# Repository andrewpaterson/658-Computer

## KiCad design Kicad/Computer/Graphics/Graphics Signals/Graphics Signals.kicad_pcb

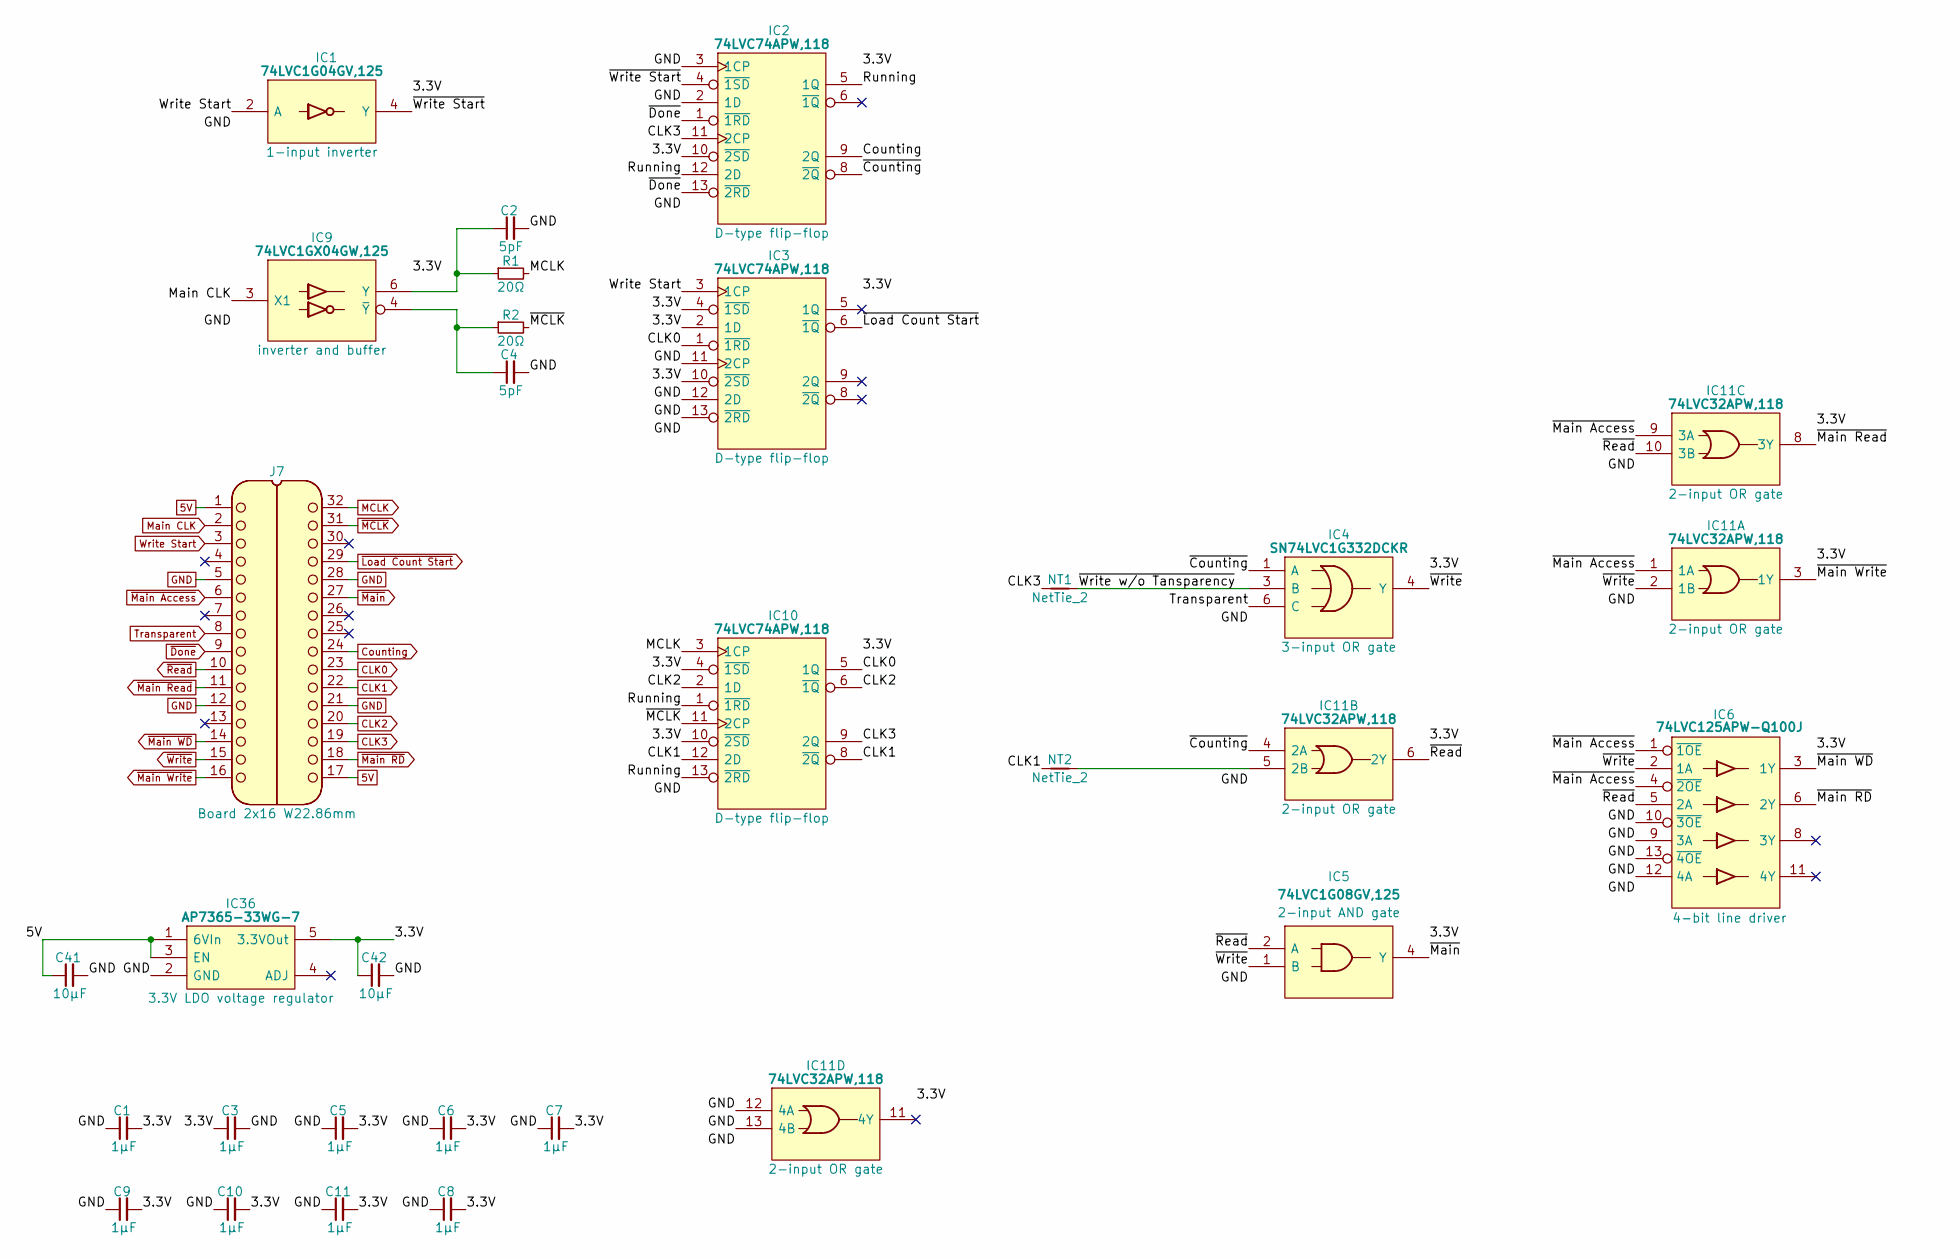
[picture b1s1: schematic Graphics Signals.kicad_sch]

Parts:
C1, C3, C5, C6, C7, C8, C9, C10, C11: 1μF; C_0805
C2, C4: 5pF; C_0805
C41, C42: 10μF; C_0805
IC1: 74LVC1G04GV,125; SOT95P275X110-5N; Manufacturer_Part_Number 74LVC1G04GV,125; Mouser Part Number 771-74LVC1G04GV
IC2, IC3, IC10: 74LVC74APW,118; SOP65P640X110-14N; Mouser Part Number 771-74LVC74APW-T
IC4: SN74LVC1G332DCKR; SOT65P210X110-6N; Mouser Part Number 595-SN74LVC1G332DCKR
IC5: 74LVC1G08GV,125; SOT95P275X110-5N; Manufacturer_Part_Number 74LVC1G08GV,125; Mouser Part Number 771-74LVC1G08GV
IC6: 74LVC125APW-Q100J; SOP65P640X110-14N; Manufacturer_Part_Number 74LVC125APW-Q100J; Mouser Part Number 771-74LVC125APWQ100J
IC9: 74LVC1GX04GW,125; SOP65P210X110-6N; Manufacturer_Part_Number 74LVC1GX04GW,125; Mouser Part Number 771-74LVC1GX04GW-G
IC11: 74LVC32APW,118; SOP65P640X110-14N; Manufacturer_Part_Number 74LVC32APW,118; Mouser Part Number 771-74LVC32APW-T
IC36: AP7365-33WG-7; SOT95P285X130-5N; Manufacturer_Part_Number AP7365-33WG-7; Mouser Part Number 621-AP7365-33WG-7
J7: Board 2x16 W22.86mm; DIP-32_Board_W22.86mm
NT1, NT2: NetTie_2; NetTie-2_SMD_Pad0.5mm
R1, R2: 20Ω; R_0805

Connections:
5V: C41.1, IC36.1 (6VIn), IC36.3 (EN), J7.1, J7.17
/3.3V: C1.2, C3.1, C5.2, C6.2, C7.2, C8.2, C9.2, C10.2, C11.2, C42.1, IC1.5 (3V), IC2.10 (~2SD), IC2.14 (3V), IC3.2 (1D), IC3.4 (~1SD), IC3.10 (~2SD), IC3.14 (3V), IC4.5 (3V), IC5.5 (3V), IC6.14 (3V), IC9.5 (3V), IC10.4 (~1SD), IC10.10 (~2SD), IC10.14 (3V), IC11.14 (3V), IC36.5 (3.3VOut)
/Running: IC2.5 (1Q), IC2.12 (2D), IC10.1 (~1RD), IC10.13 (~2RD)
/~Counting: IC2.8 (~2Q), IC4.1 (A), IC11.4 (2A)
/~Write Start: IC1.4 (Y), IC2.4 (~1SD)
/~Write w/o Tansparency: IC4.3 (B), NT1.2
CLK0: IC3.1 (~1RD), IC10.5 (1Q), J7.23
CLK1: IC10.8 (~2Q), IC10.12 (2D), J7.22, NT2.1
CLK2: IC10.2 (1D), IC10.6 (~1Q), J7.20
CLK3: IC2.11 (2CP), IC10.9 (2Q), J7.19, NT1.1
Counting: IC2.9 (2Q), J7.24
GND: C1.1, C2.2, C3.2, C4.2, C5.1, C6.1, C7.1, C8.1, C9.1, C10.1, C11.1, C41.2, C42.2, IC1.3 (GND), IC2.2 (1D), IC2.3 (1CP), IC2.7 (GND), IC3.7 (GND), IC3.11 (2CP), IC3.12 (2D), IC3.13 (~2RD), IC4.2 (GND), IC5.3 (GND), IC6.7 (GND), IC6.9 (3A), IC6.10 (~3OE), IC6.12 (4A), IC6.13 (~4OE), IC9.2 (GND), IC10.7 (GND), IC11.7 (GND), IC11.12 (4A), IC11.13 (4B), IC36.2 (GND), J7.5, J7.12, J7.21, J7.28
MCLK: IC10.3 (1CP), J7.32, R1.2
Main CLK: IC9.3 (X1), J7.2
unnamed: C2.1, IC9.6 (Y), R1.1
unnamed: C4.1, IC9.4 (~Y), R2.1
unnamed: IC11.5 (2B), NT2.2
Transparent: IC4.6 (C), J7.8
Write Start: IC1.2 (A), IC3.3 (1CP), J7.3
~Done: IC2.1 (~1RD), IC2.13 (~2RD), J7.9
~Load Count Start: IC3.6 (~1Q), J7.29
~MCLK: IC10.11 (2CP), J7.31, R2.2
~Main Access: IC6.1 (~1OE), IC6.4 (~2OE), IC11.1 (1A), IC11.9 (3A), J7.6
~Main RD: IC6.6 (2Y), J7.18
~Main Read: IC11.8 (3Y), J7.11
~Main WD: IC6.3 (1Y), J7.14
~Main Write: IC11.3 (1Y), J7.16
~Main: IC5.4 (Y), J7.27
~Read: IC5.2 (A), IC6.5 (2A), IC11.6 (2Y), IC11.10 (3B), J7.10
~Write: IC4.4 (Y), IC5.1 (B), IC6.2 (1A), IC11.2 (1B), J7.15

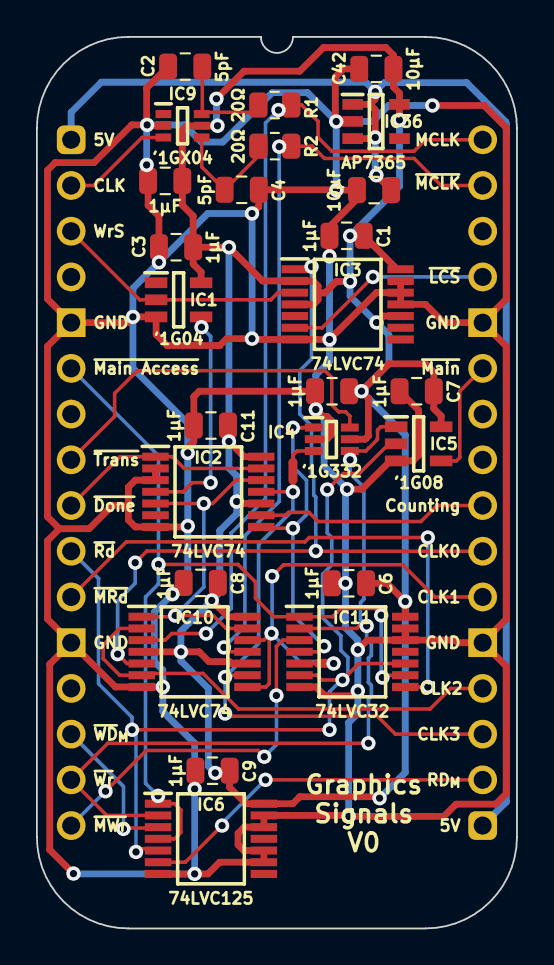
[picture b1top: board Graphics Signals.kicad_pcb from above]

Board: 2 copper layers, 26.7 x 49.5 mm, 28 parts (0 on the bottom side), 30 nets.

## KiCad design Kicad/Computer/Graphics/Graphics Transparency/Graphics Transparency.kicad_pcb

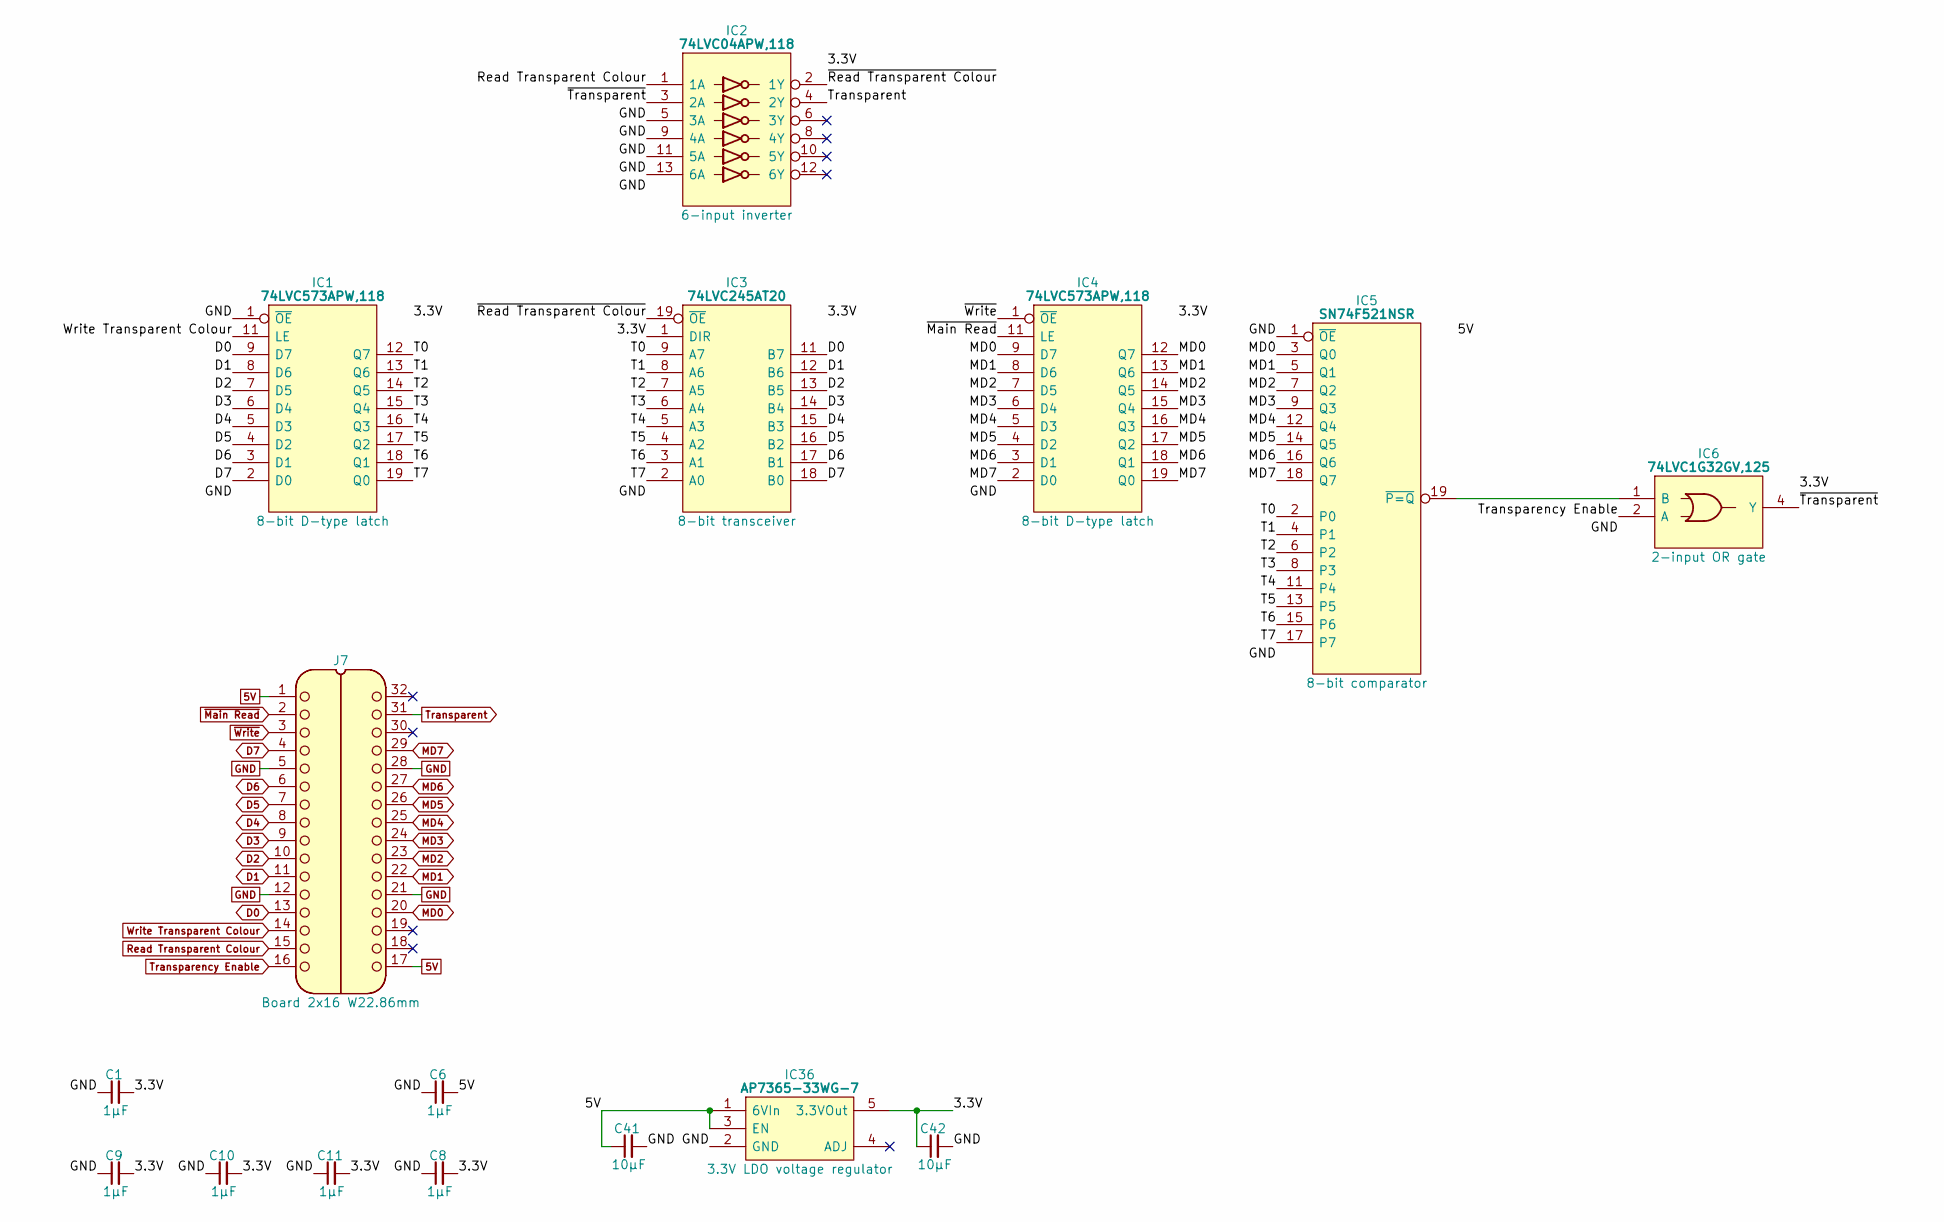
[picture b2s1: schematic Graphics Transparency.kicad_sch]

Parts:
C1, C6, C8, C9, C10, C11: 1μF; C_0805
C41, C42: 10μF; C_0805
IC1, IC4: 74LVC573APW,118; SOP65P640X110-20N; Mouser Part Number 771-74LVC573APW-T
IC2: 74LVC04APW,118; SOP65P640X110-14N; Manufacturer_Part_Number 74LVC04APW,118; Mouser Part Number 771-74LVC04APW-T
IC3: 74LVC245AT20; SOP65P640X120-20N; Manufacturer_Part_Number 74LVC245AT20-13; Mouser Part Number 621-74LVC245AT20-13
IC5: SN74F521NSR; SOIC127P780X200-20N; Mouser Part Number 595-SN74F521NSR
IC6: 74LVC1G32GV,125; SOT95P275X110-5N; Manufacturer_Part_Number 74LVC1G32GV,125; Mouser Part Number 771-LVC1G32GV125
IC36: AP7365-33WG-7; SOT95P285X130-5N; Manufacturer_Part_Number AP7365-33WG-7; Mouser Part Number 621-AP7365-33WG-7
J7: Board 2x16 W22.86mm; DIP-32_Board_W22.86mm

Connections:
5V: C6.2, C41.1, IC5.20 (5V), IC36.1 (6VIn), IC36.3 (EN), J7.1, J7.17
/3.3V: C1.2, C8.2, C9.2, C10.2, C11.2, C42.1, IC1.20 (3V), IC2.14 (3V), IC3.1 (DIR), IC3.20 (3V), IC4.20 (3V), IC6.5 (3V), IC36.5 (3.3VOut)
/T0: IC1.12 (Q7), IC3.9 (A7), IC5.2 (P0)
/T1: IC1.13 (Q6), IC3.8 (A6), IC5.4 (P1)
/T2: IC1.14 (Q5), IC3.7 (A5), IC5.6 (P2)
/T3: IC1.15 (Q4), IC3.6 (A4), IC5.8 (P3)
/T4: IC1.16 (Q3), IC3.5 (A3), IC5.11 (P4)
/T5: IC1.17 (Q2), IC3.4 (A2), IC5.13 (P5)
/T6: IC1.18 (Q1), IC3.3 (A1), IC5.15 (P6)
/T7: IC1.19 (Q0), IC3.2 (A0), IC5.17 (P7)
/~Read Transparent Colour: IC2.2 (1Y), IC3.19 (~OE)
/~Transparent: IC2.3 (2A), IC6.4 (Y)
D0: IC1.9 (D7), IC3.11 (B7), J7.13
D1: IC1.8 (D6), IC3.12 (B6), J7.11
D2: IC1.7 (D5), IC3.13 (B5), J7.10
D3: IC1.6 (D4), IC3.14 (B4), J7.9
D4: IC1.5 (D3), IC3.15 (B3), J7.8
D5: IC1.4 (D2), IC3.16 (B2), J7.7
D6: IC1.3 (D1), IC3.17 (B1), J7.6
D7: IC1.2 (D0), IC3.18 (B0), J7.4
GND: C1.1, C6.1, C8.1, C9.1, C10.1, C11.1, C41.2, C42.2, IC1.1 (~OE), IC1.10 (GND), IC2.5 (3A), IC2.7 (GND), IC2.9 (4A), IC2.11 (5A), IC2.13 (6A), IC3.10 (GND), IC4.10 (GND), IC5.1 (~OE), IC5.10 (GND), IC6.3 (GND), IC36.2 (GND), J7.5, J7.12, J7.21, J7.28
MD0: IC4.9 (D7), IC4.12 (Q7), IC5.3 (Q0), J7.20
MD1: IC4.8 (D6), IC4.13 (Q6), IC5.5 (Q1), J7.22
MD2: IC4.7 (D5), IC4.14 (Q5), IC5.7 (Q2), J7.23
MD3: IC4.6 (D4), IC4.15 (Q4), IC5.9 (Q3), J7.24
MD4: IC4.5 (D3), IC4.16 (Q3), IC5.12 (Q4), J7.25
MD5: IC4.4 (D2), IC4.17 (Q2), IC5.14 (Q5), J7.26
MD6: IC4.3 (D1), IC4.18 (Q1), IC5.16 (Q6), J7.27
MD7: IC4.2 (D0), IC4.19 (Q0), IC5.18 (Q7), J7.29
unnamed: IC5.19 (~P=Q), IC6.1 (B)
Read Transparent Colour: IC2.1 (1A), J7.15
Transparency Enable: IC6.2 (A), J7.16
Transparent: IC2.4 (2Y), J7.31
Write Transparent Colour: IC1.11 (LE), J7.14
~Main Read: IC4.11 (LE), J7.2
~Write: IC4.1 (~OE), J7.3

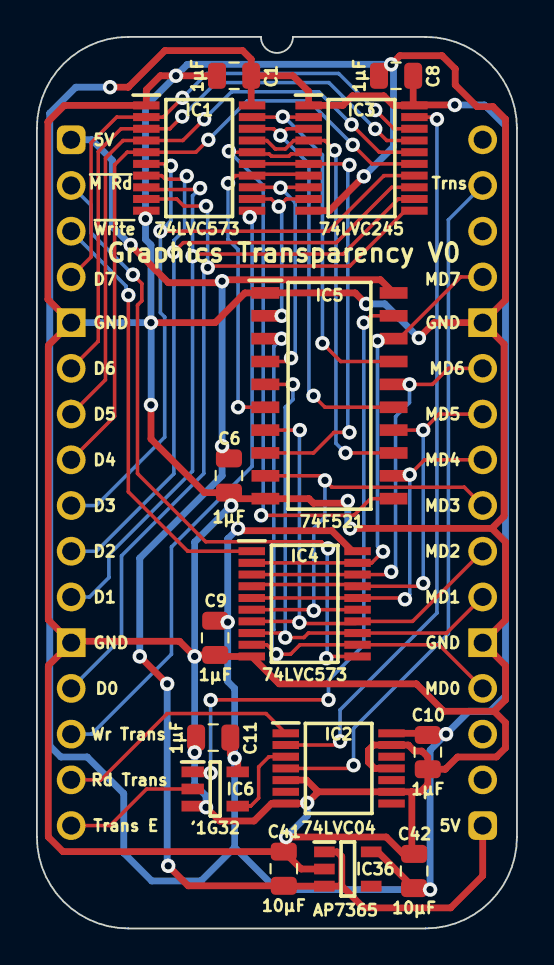
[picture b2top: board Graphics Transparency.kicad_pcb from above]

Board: 2 copper layers, 26.7 x 49.5 mm, 16 parts (0 on the bottom side), 36 nets.

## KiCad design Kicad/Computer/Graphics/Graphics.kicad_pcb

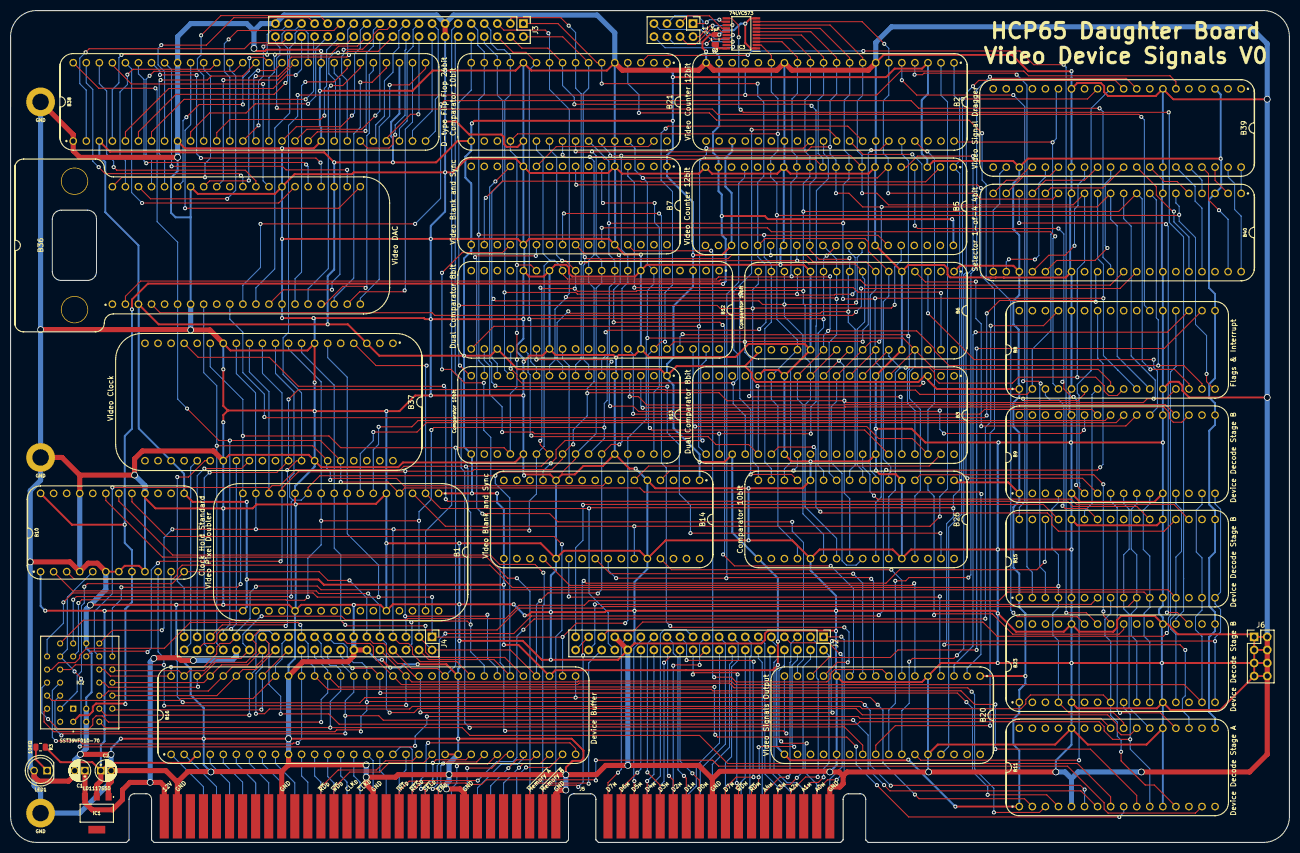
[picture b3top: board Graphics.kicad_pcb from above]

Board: 2 copper layers, 248.9 x 161.9 mm, 41 parts (0 on the bottom side), 267 nets.

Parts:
B1: Video Pixel Doubler; HCP65_Video_Pixel_Doubler
B2, B5: Video Counter 12bit; HCP65_Video_Counter_12bit
B3, B12: Dual Comparator 8bit; HCP65_Dual_Comparator_8bit
B6, B13, B21, B26: Comparator 10bit; HCP65_Comparator_10bit
B7, B14: Video Blank and Sync; HCP65_Video_Blank_and_Sync
B8: Flags & Interrupt; HCP65_Flags_Interrupt
B9, B15, B23: Device Decode Stage B; HCP65_Device_Decode_Stage_B
B10: Clock Hold Standard; HCP65_Clock_Hold_Standard
B11: Device Decode Stage A; HCP65_Device_Decode_Stage_A
B16: Device Buffer; HCP65_Device_Buffer
B20: Video Signals Output; HCP65_Video_Output_Signals
B36: Video DAC; HCP65_Video_DAC
B37: Video Clock; HCP65_Video_Clock
B38: D-type Flip Flop 24bit; HCP65_D_Flip_Flop_24bit
B39: Video Signal Dragger; HCP65_Video_Signal_Dragger
B40: Selector 1-of-4 4bit with Input; HCP65_Selector_1_of_4_4bit_with_Input
C1: 10μF; CP_Radial_D4.0mm_P2.00mm
C2: 100μF; CP_Radial_D4.0mm_P2.00mm
C3: ?μF; C_0805
H1, H9, H19: MountingHole_Pad; HCP65_MountingHole_M3_
IC1: LD1117S50C; LD1117S33C
IC2: SST39VF010-70-4I-NHE; 5408803224008
IC3: 74LVC573APW,118; SOP65P640X110-20N
J1, J6: Conn_01x08_Pin; PinHeader_2x04_P2.54mm_Vertical
J2, J3, J4: Conn_01x40_Pin; PinHeader_2x20_P2.54mm_Vertical
J5: 395-098-520-350; 98pin Edge Connector
LED1: LED; LED_D5.0mm
R3: 10KΩ; R_0805

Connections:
/3.3V: B2.19 (IR0), B5.19 (IR0), B5.40 (~CLK), B10.8 (H0_{REG}), B10.24 (3.3V), C3.2, IC2.32 (3V), IC3.20 (3V)
/5V: B1.1 (5V), B1.17 (5V), B2.3 (5V), B2.23 (5V), B3.3 (5V), B3.23 (5V), B5.3 (5V), B5.23 (5V), B6.1 (5V), B6.17 (5V), B7.1 (5V), B7.17 (5V), B8.1 (5V), B8.17 (5V), B9.1 (5V), B9.17 (5V), B10.1 (5V), B10.13 (5V), B11.1 (5V), B11.17 (5V), B12.3 (5V), B12.23 (5V), B13.1 (5V), B13.17 (5V), B14.1 (5V), B14.17 (5V), B15.1 (5V), B15.17 (5V), B16.3 (5V), B16.35 (5V), B20.1 (5V), B20.17 (5V), B21.1 (5V), B21.17 (5V), B23.1 (5V), B23.17 (5V), B26.1 (5V), B26.17 (5V), B36.3 (5V), B36.23 (5V), B37.3 (5V), B37.23 (5V), B38.3 (5V), B38.31 (5V), B39.3 (5V), B39.23 (5V), B40.3 (5V), B40.23 (5V), C2.1, IC1.2 (5.0VOut), R3.2
/12V: C1.1, IC1.3 (15VIn), J4.32, J5.B1
/A0: B9.13 (A0), B15.13 (A0), B16.64 (A0), B23.13 (A0), IC2.12 (A0), J4.31
/A0_{D}: B16.1 (A0_{IN}), J5.A4
/A0_{M}: J2.1, J5.D17
/A1: B9.11 (A1), B15.11 (A1), B16.63 (A1), B23.11 (A1), IC2.11 (A1), J4.30
/A1_{D}: B16.2 (A1_{IN}), J5.A5
/A1_{M}: J2.2, J5.D16
/A2: B9.10 (A2), B15.10 (A2), B16.62 (A2), B23.10 (A2), IC2.10 (A2), J4.29
/A2_{D}: B16.4 (A2_{IN}), J5.A6
/A2_{M}: J2.3, J5.D15
/A3: B11.13 (A3), B15.8 (~E2), B16.61 (A3), B23.8 (~E2), IC2.9 (A3), J4.28
/A3_{D}: B16.5 (A3_{IN}), J5.A7
/A3_{M}: J2.4, J5.D14
/A4: B11.11 (A4), B16.60 (A4), B23.9 (E3), IC2.8 (A4), J4.27
/A4_{D}: B16.6 (A4_{IN}), J5.A8
/A4_{M}: J2.5, J5.D13
/A5: B16.59 (A5), IC2.7 (A5), J4.26
/A5_{D}: B16.7 (A5_{IN}), J5.A9
/A5_{M}: J2.6, J5.D12
/A6: B16.58 (A6), IC2.6 (A6), J4.25
/A6_{D}: B16.8 (A6_{IN}), J5.A10
/A6_{M}: J2.7, J5.C18
/A7: B16.57 (A7), IC2.5 (A7), J4.24
/A7_{D}: B16.9 (A7_{IN}), J5.A11
/A7_{M}: J2.8, J5.C17
/A8: B16.56 (A8), IC2.27 (A8), J4.23
/A8_{D}: B16.11 (A8_{IN}), J5.A12
/A8_{M}: J2.9, J5.C16
/A9: B16.54 (A9), IC2.26 (A9), J4.22
/A9_{D}: B16.12 (A9_{IN}), J5.A13
/A9_{M}: J2.10, J5.C15
/A10: B11.10 (A10), B16.53 (A10), IC2.23 (A10), J4.21
/A10_{D}: B16.13 (A10_{IN}), J5.A14
/A10_{M}: J2.11, J5.C14
/A11: B11.9 (A11), B16.52 (A11), IC2.25 (A11), J4.20
/A11_{D}: B16.14 (A11_{IN}), J5.A15
/A11_{M}: J2.12, J5.C13
/A12: B11.8 (A12), B16.51 (A12), IC2.4 (A12), J4.19
/A12_{D}: B16.15 (A12_{IN}), J5.A16
/A12_{M}: J2.13, J5.C12
/A13: B11.7 (A13), B16.50 (A13), IC2.28 (A13), J4.18
/A13_{D}: B16.16 (A13_{IN}), J5.A17
/A13_{M}: J2.14, J5.C11
/A14: B11.6 (A14), B16.49 (A14), IC2.29 (A14), J4.17
/A14_{D}: B16.17 (A14_{IN}), J5.A18
/A14_{M}: J2.15, J5.C10
/A15: B11.4 (A15), B16.48 (A15), J4.16
/A15_{D}: B16.19 (A16_{IN}), J5.A19
/A15_{M}: J2.16, J5.C9
/A16: B11.3 (A16), B16.47 (A16), J4.15
/A16_{D}: B16.18 (A15_{IN}), J5.A20
/A16_{M}: J2.17, J5.C8
/A17_{M}: J2.18, J5.C7
/A18_{M}: J2.19, J5.C6
/A19_{M}: J2.20, J5.C5
/A20_{M}: J2.21, J5.C4
/Advance Pixel: B1.31 (Selected_Pattern), J3.11
/Blue0: B38.28 (IN0), J3.15
/Blue0 _{HALF CYCLE}: B36.20 (Blue0), B38.29 (OUT0)
/Blue1: B38.27 (IN1), J3.16
/Blue1 _{HALF CYCLE}: B36.19 (Blue1), B38.30 (OUT1)
/Blue2: B38.26 (IN2), J3.17
/Blue2 _{HALF CYCLE}: B36.18 (Blue2), B38.32 (OUT2)
/Blue3: B38.25 (IN3), J3.18
/Blue3 _{HALF CYCLE}: B36.17 (Blue3), B38.33 (OUT3)
/Blue4: B38.24 (IN4), J3.19
/Blue4 _{HALF CYCLE}: B36.16 (Blue4), B38.34 (OUT4)
/Blue5: B38.23 (IN5), J3.20
/Blue5 _{HALF CYCLE}: B36.15 (Blue5), B38.35 (OUT5)
/Blue6: B38.22 (IN6), J3.21
/Blue6 _{HALF CYCLE}: B36.13 (Blue6), B38.36 (OUT6)
/Blue7: B38.21 (IN7), J3.22
/Blue7 _{HALF CYCLE}: B36.12 (Blue7), B38.38 (OUT7)
/D0: B1.16 (D0), B2.15 (D0), B3.15 (D0), B5.15 (D0), B6.20 (D0), B8.16 (D0), B12.15 (D0), B13.20 (D0), B16.43 (D7), B21.20 (D0), B26.20 (D0), B37.15 (D0), B40.6 (D0), IC2.13 (DQ0), IC3.2 (D0), J4.8
/D0_{D}: B16.31 (D0_{IN/OUT}), J5.A28
/D0_{M}: J2.24, J5.D8
/D1: B1.15 (D1), B2.13 (D1), B3.13 (D1), B5.13 (D1), B6.22 (D1), B8.15 (D1), B12.13 (D1), B13.22 (D1), B16.41 (D6), B21.22 (D1), B26.22 (D1), B37.13 (D1), B40.8 (D1), IC2.14 (DQ1), IC3.3 (D1), J4.7
/D1_{D}: B16.30 (D1_{IN/OUT}), J5.A27
/D1_{M}: J2.25, J5.D7
/D2: B1.14 (D2), B2.12 (D2), B3.12 (D2), B5.12 (D2), B6.23 (D2), B8.14 (D2), B12.12 (D2), B13.23 (D2), B16.40 (D5), B21.23 (D2), B26.23 (D2), B37.12 (D2), B40.9 (D2), IC2.15 (DQ2), IC3.4 (D2), J4.6
/D2_{D}: B16.29 (D2_{IN/OUT}), J5.A26
/D2_{M}: J2.26, J5.D6
/D3: B1.13 (D3), B2.11 (D3), B3.11 (D3), B5.11 (D3), B6.24 (D3), B8.13 (D3), B12.11 (D3), B13.24 (D3), B16.39 (D4), B21.24 (D3), B26.24 (D3), B37.11 (D3), B40.10 (D3), IC2.17 (DQ3), IC3.5 (D3), J4.5
/D3_{D}: B16.28 (D3_{IN/OUT}), J5.A25
/D3_{M}: J2.27, J5.D5
/D4: B1.11 (D4), B2.10 (D4), B3.10 (D4), B5.10 (D4), B6.25 (D4), B8.11 (D4), B12.10 (D4), B13.25 (D4), B16.38 (D3), B21.25 (D4), B26.25 (D4), B37.10 (D4), B40.11 (D4), IC2.18 (DQ4), IC3.6 (D4), J4.4
/D4_{D}: B16.27 (D4_{IN/OUT}), J5.A24
/D4_{M}: J2.28, J5.D4
/D5: B1.10 (D5), B2.9 (D5), B3.9 (D5), B5.9 (D5), B6.26 (D5), B8.10 (D5), B12.9 (D5), B13.26 (D5), B16.37 (D2), B21.26 (D5), B26.26 (D5), B37.9 (D5), B40.12 (D5), IC2.19 (DQ5), IC3.7 (D5), J4.3
/D5_{D}: B16.26 (D5_{IN/OUT}), J5.A23
/D5_{M}: J2.29, J5.D3
/D6: B1.9 (D6), B2.8 (D6), B3.8 (D6), B5.8 (D6), B6.27 (D6), B8.9 (D6), B12.8 (D6), B13.27 (D6), B16.36 (D1), B21.27 (D6), B26.27 (D6), B37.8 (D6), B40.13 (D6), IC2.20 (DQ6), IC3.8 (D6), J4.2
/D6_{D}: B16.25 (D6_{IN/OUT}), J5.A22
/D6_{M}: J2.30, J5.D2
/D7: B1.8 (D7), B2.6 (D7), B3.6 (D7), B5.6 (D7), B6.29 (D7), B8.8 (D7), B12.6 (D7), B13.29 (D7), B16.34 (D0), B21.29 (D7), B26.29 (D7), B37.6 (D7), B40.15 (D7), IC2.21 (DQ7), IC3.9 (D7), J4.1
/D7_{D}: B16.24 (D7_{IN/OUT}), J5.A21
/D7_{M}: J2.31, J5.D1
/First Pixel: B5.17 (CLK), B14.25 (First), B20.9 (First_Pixel)
/First Pixel _{HALF CYCLE}: B7.8 (~CLK), B20.24 (First_Pixel_{OUT})
/First Row: B7.25 (First), B20.11 (First_Row)
/GND: B1.5 (GND), B1.12 (GND), B1.21 (GND), B1.28 (GND), B2.7 (GND), B2.14 (GND), B2.20 (IR1), B2.27 (GND), B2.34 (GND), B3.7 (GND), B3.14 (GND), B3.16 (~OE), B3.27 (GND), B3.34 (GND), B5.7 (GND), B5.14 (GND), B5.20 (IR1), B5.27 (GND), B5.34 (GND), B6.5 (GND), B6.12 (GND), B6.21 (GND), B6.28 (GND), B7.5 (GND), B7.12 (GND), B7.21 (GND), B7.28 (GND), B8.5 (GND), B8.12 (GND), B8.21 (GND), B8.28 (GND), B9.5 (GND), B9.12 (GND), B9.21 (GND), B9.28 (GND), B10.4 (GND), B10.6 (H2_{REG}), B10.7 (H1_{REG}), B10.9 (GND), B10.16 (GND), B10.21 (GND), B11.5 (GND), B11.12 (GND), B11.21 (GND), B11.28 (GND), B12.7 (GND), B12.14 (GND), B12.16 (~OE), B12.27 (GND), B12.34 (GND), B13.5 (GND), B13.12 (GND), B13.21 (GND), B13.28 (GND), B14.5 (GND), B14.12 (GND), B14.21 (GND), B14.28 (GND), B15.5 (GND), B15.12 (GND), B15.21 (GND), B15.28 (GND), B16.10 (GND), B16.22 (S_{IN}), B16.23 (GND), B16.42 (GND), B16.55 (GND), B20.5 (GND), B20.12 (GND), B20.21 (GND), B20.28 (GND), B21.5 (GND), B21.12 (GND), B21.21 (GND), B21.28 (GND), B23.5 (GND), B23.12 (GND), B23.21 (GND), B23.28 (GND), B26.5 (GND), B26.12 (GND), B26.21 (GND), B26.28 (GND), B36.7 (GND), B36.14 (GND), B36.27 (GND), B36.34 (GND), B37.7 (GND), B37.14 (GND), B37.27 (GND), B37.34 (GND), B38.1 (~OE), B38.9 (GND), B38.20 (GND), B38.37 (GND), B38.48 (GND), B39.7 (GND), B39.14 (GND), B39.27 (GND), B39.34 (GND), B40.7 (GND), B40.14 (GND), B40.27 (GND), B40.34 (GND), C1.2, C2.2, C3.1, H1.1 (GND), H9.1 (GND), H19.1 (GND), IC1.1 (GND), IC2.2 (A16), IC2.3 (A15), IC2.16 (GND), IC3.1 (~OE), IC3.10 (GND), J2.32, J2.33, J3.13, J3.14, J3.39, J4.12, J4.13, J4.14, J5.B2, J5.B10, J5.B17, J5.B24, J5.B31, J5.D9, J5.D18, J6.1, J6.2, J6.3, J6.4, J6.5, J6.6, J6.7, J6.8, LED1.2 (A)
/Green0: B38.19 (IN8), J3.23
/Green0 _{HALF CYCLE}: B36.32 (Green0), B38.39 (OUT8)
/Green1: B38.18 (IN9), J3.24
/Green1 _{HALF CYCLE}: B36.33 (Green1), B38.40 (OUT9)
/Green2: B38.17 (IN10), J3.25
/Green2 _{HALF CYCLE}: B36.35 (Green2), B38.41 (OUT10)
/Green3: B38.16 (IN11), J3.26
/Green3 _{HALF CYCLE}: B36.36 (Green3), B38.42 (OUT11)
/Green4: B38.15 (IN12), J3.27
/Green4 _{HALF CYCLE}: B36.37 (Green4), B38.43 (OUT12)
/Green5: B38.14 (IN13), J3.28
/Green5 _{HALF CYCLE}: B36.38 (Green5), B38.44 (OUT13)
/Green6: B38.13 (IN14), J3.29
/Green6 _{HALF CYCLE}: B36.39 (Green6), B38.45 (OUT14)
/Green7: B38.12 (IN15), J3.30
/Green7 _{HALF CYCLE}: B36.40 (Green7), B38.46 (OUT15)
/H0_{D}: B10.17 (H0_{OUT}), J5.A31
/H1_{D}: B10.18 (H1_{OUT}), J5.A30
/H2_{D}: B10.19 (H2_{OUT}), J5.A29
/H3: B2.29 (R3), B3.21 (C0), B12.21 (C0)
/H4: B2.30 (R4), B3.22 (C1), B12.22 (C1)
/H5: B2.31 (R5), B3.24 (C2), B12.24 (C2)
/H6: B2.32 (R6), B3.25 (C3), B12.25 (C3)
/H7: B2.33 (R7), B3.35 (C4), B12.35 (C4)
/H8: B2.35 (R8), B3.36 (C5), B12.36 (C5)
/H9: B2.36 (R9), B3.37 (C6), B12.37 (C6)
/H10: B2.37 (R10), B3.38 (C7), B12.38 (C7)
/Horizontal Blank: B14.29 (Blank), B20.7 (Horizontal_Blank)
/Horizontal Blank _{CYCLE 3H}: B39.38 (Horizontal_Blank__{CYCLE_3H}), B40.2 (A2)
/Horizontal Blank _{CYCLE 3}: B39.33 (Horizontal_Blank__{CYCLE_3}), B40.5 (B2)
/Horizontal Blank _{CYCLE 4H}: B39.29 (Horizontal_Blank__{CYCLE_4H}), B40.17 (C2)
/Horizontal Blank _{CYCLE 4}: B39.24 (Horizontal_Blank__{CYCLE_4}), B40.20 (E2)
/Horizontal Blank _{FINAL}: B36.2 (Horizontal_Blank), B40.31 (Y1)
/Horizontal Blank _{HALF CYCLE}: B20.27 (Horizontal_Blank_{OUT}), B39.11 (Horizontal_Blank__{HALF_CYCLE})
/Horizontal Sync: B14.22 (Sync), B20.4 (Horizontal_Sync)
/Horizontal Sync Polarity: B8.19 (F1), B20.3 (Horizontal_Sync_Polarity)
/Horizontal Sync _{CYCLE 3H}: B39.37 (Horizontal_Sync__{CYCLE_3H}), B40.39 (A3)
/Horizontal Sync _{CYCLE 3}: B39.32 (Horizontal_Sync__{CYCLE_3}), B40.36 (B3)
/Horizontal Sync _{CYCLE 4H}: B39.28 (Horizontal_Sync__{CYCLE_4H}), B40.24 (C3)
/Horizontal Sync _{CYCLE 4}: B39.22 (Horizontal_Sync__{CYCLE_4}), B40.21 (E3)
/Horizontal Sync _{FINAL}: B36.4 (Horizontal_Sync), B40.32 (Y0)
/Horizontal Sync _{HALF CYCLE}: B20.29 (Horizontal_Sync_{OUT}), B39.12 (Horizontal_Sync__{HALF_CYCLE})
/Last Pixel+1: B14.24 (Last+1), B20.10 (Last_Pixel+1)
/Last Pixel+1 _{HALF CYCLE}: B20.23 (Last_Pixel+1_{OUT}), J3.12
/Last Row+1: B7.24 (Last+1), B20.13 (Last_Row+1)
/Memory Frame: B8.20 (F2), J2.35
/PL0: IC3.19 (Q0), J1.8
/PL1: IC3.18 (Q1), J1.7
/PL2: IC3.17 (Q2), J1.6
/PL3: IC3.16 (Q3), J1.5
/PL4: IC3.15 (Q4), J1.4
/PL5: IC3.14 (Q5), J1.3
/PL6: IC3.13 (Q6), J1.2
/PL7: IC3.12 (Q7), J1.1
/Palette Write: B8.22 (F3), J3.40
/Pixel CLK_{0}: B1.4 (CLK), B20.2 (~Pixel_CLK), B36.6 (~CLK), B37.36 (Pixel_CLK_{0}), B38.56 (CLK), J4.33
/Pixel CLK_{1}: B2.17 (CLK), B37.33 (Pixel_CLK_{1}), B39.6 (Pixel_CLK), J4.35
/Pixel CLK_{2}: B37.29 (Pixel_CLK_{2}), J4.37
/Pixel CLK_{3}: B37.26 (Pixel_CLK_{3}), J4.39
/Read Address Bank: B15.7 (Y4_{R}), J2.38
/Read Address High: B15.29 (Y3_{R}), J2.39
/Read Address Low: B15.30 (Y2_{R}), J2.40
/Read Flags: B8.6 (Read_Flags), B15.32 (Y0_{R})
/Read Horizontal High: B2.4 (Read_Count_High), B15.2 (Y7_{R})
/Read Horizontal Low: B2.5 (Read_Count_Low), B15.3 (Y6_{R})
/Read Vertical High: B5.4 (Read_Count_High), B9.6 (Y5_{R})
/Read Vertical Low: B5.5 (Read_Count_Low), B9.7 (Y4_{R})
/Red0: B38.11 (IN16), J3.31
/Red0 _{HALF CYCLE}: B36.21 (Red0), B38.47 (OUT16)
/Red1: B38.10 (IN17), J3.32
/Red1 _{HALF CYCLE}: B36.22 (Red1), B38.49 (OUT17)
/Red2: B38.8 (IN18), J3.33
/Red2 _{HALF CYCLE}: B36.24 (Red2), B38.50 (OUT18)
/Red3: B38.7 (IN19), J3.34
/Red3 _{HALF CYCLE}: B36.25 (Red3), B38.51 (OUT19)
/Red4: B38.6 (IN20), J3.35
/Red4 _{HALF CYCLE}: B36.26 (Red4), B38.52 (OUT20)
/Red5: B38.5 (IN21), J3.36
/Red5 _{HALF CYCLE}: B36.28 (Red5), B38.53 (OUT21)
/Red6: B38.4 (IN22), J3.37
/Red6 _{HALF CYCLE}: B36.29 (Red6), B38.54 (OUT22)
/Red7: B38.2 (IN23), J3.38
/Red7 _{HALF CYCLE}: B36.30 (Red7), B38.55 (OUT23)
/Row0: B5.25 (R0), B6.6 (C0), B13.6 (C0), B21.6 (C0), B26.6 (C0), J3.1
/Row1: B5.26 (R1), B6.7 (C1), B13.7 (C1), B21.7 (C1), B26.7 (C1), J3.2
/Row2: B5.28 (R2), B6.8 (C2), B13.8 (C2), B21.8 (C2), B26.8 (C2), J3.3
/Row3: B5.29 (R3), B6.9 (C3), B13.9 (C3), B21.9 (C3), B26.9 (C3), J3.4
/Row4: B5.30 (R4), B6.10 (C4), B13.10 (C4), B21.10 (C4), B26.10 (C4), J3.5
/Row5: B5.31 (R5), B6.11 (C5), B13.11 (C5), B21.11 (C5), B26.11 (C5), J3.6
/Row6: B5.32 (R6), B6.13 (C6), B13.13 (C6), B21.13 (C6), B26.13 (C6), J3.7
/Row7: B5.33 (R7), B6.14 (C7), B13.14 (C7), B21.14 (C7), B26.14 (C7), J3.8
/Row8: B5.35 (R8), B6.15 (C8), B13.15 (C8), B21.15 (C8), B26.15 (C8), J3.9
/Row9: B5.36 (R9), B6.16 (C9), B13.16 (C9), B21.16 (C9), B26.16 (C9), J3.10
/Vertical Blank: B7.29 (Blank), B20.8 (Vertical_Blank)
/Vertical Blank _{CYCLE 3H}: B39.40 (Vertical_Blank__{CYCLE_3H}), B40.1 (A0)
/Vertical Blank _{CYCLE 3}: B39.36 (Vertical_Blank__{CYCLE_3}), B40.4 (B0)
/Vertical Blank _{CYCLE 4H}: B39.31 (Vertical_Blank__{CYCLE_4H}), B40.16 (C0)
/Vertical Blank _{CYCLE 4}: B39.26 (Vertical_Blank__{CYCLE_4}), B40.19 (E0)
/Vertical Blank _{FINAL}: B36.10 (Vertical_Blank), B40.29 (Y3)
/Vertical Blank _{HALF CYCLE}: B20.25 (Vertical_Blank_{OUT}), B39.9 (Vertical_Blank__{HALF_CYCLE})
/Vertical Sync: B7.22 (Sync), B20.15 (Vertical_Sync)
/Vertical Sync Polarity: B8.18 (F0), B20.14 (Vertical_Sync_Polarity)
/Vertical Sync _{CYCLE 3H}: B39.39 (Vertical_Sync__{CYCLE_3H}), B40.40 (A1)
/Vertical Sync _{CYCLE 3}: B39.35 (Vertical_Sync__{CYCLE_3}), B40.37 (B1)
/Vertical Sync _{CYCLE 4H}: B39.30 (Vertical_Sync__{CYCLE_4H}), B40.25 (C1)
/Vertical Sync _{CYCLE 4}: B39.25 (Vertical_Sync__{CYCLE_4}), B40.22 (E1)
/Vertical Sync _{FINAL}: B36.11 (Vertical_Sync), B40.30 (Y2)
/Vertical Sync _{HALF CYCLE}: B20.26 (Vertical_Sync_{OUT}), B39.10 (Vertical_Sync__{HALF_CYCLE})
/Write Clear Interrupt: B8.3 (Write_Clear_Interrupt), B15.26 (Y1_{W})
/Write Clock Select: B15.22 (Y5_{W}), B37.17 (Write_Clock_Select)
/Write Flags: B8.7 (Write_Flags), B15.27 (Y0_{W})
/Write Horizontal Back Porch End: B9.26 (Y1_{W}), B12.33 (Write_B)
/Write Horizontal Back Porch Start: B9.27 (Y0_{W}), B12.26 (Write_A)
/Write Horizontal Front Porch Start: B3.26 (Write_A), B15.20 (Y6_{W})
/Write Horizontal Shift Pattern High: B1.7 (Write_Pattern_High), B9.24 (Y3_{W})
/Write Horizontal Shift Pattern Low: B1.6 (Write_Pattern_Low), B9.25 (Y2_{W})
/Write Horiztonal Sync Start: B3.33 (Write_B), B15.19 (Y7_{W})
/Write Palette Byte: B23.20 (Y6_{W}), IC3.11 (LE)
/Write Vertical Back Porch End High: B23.24 (Y3_{W}), B26.3 (Write_A_High)
/Write Vertical Back Porch End Low: B23.25 (Y2_{W}), B26.4 (Write_A_Low)
/Write Vertical Back Porch Start High: B21.3 (Write_A_High), B23.26 (Y1_{W})
/Write Vertical Back Porch Start Low: B21.4 (Write_A_Low), B23.27 (Y0_{W})
/Write Vertical Front Porch Start High: B6.3 (Write_A_High), B9.22 (Y5_{W})
/Write Vertical Front Porch Start Low: B6.4 (Write_A_Low), B9.23 (Y4_{W})
/Write Vertical Sync Start High: B9.19 (Y7_{W}), B13.3 (Write_A_High)
/Write Vertical Sync Start Low: B9.20 (Y6_{W}), B13.4 (Write_A_Low)
/Write Video Signal Delay: B23.19 (Y7_{W}), B40.18 (Write_Select)
/~A3: B9.8 (~E2), B11.20 (~A3)
/~A4: B9.9 (E3), B11.22 (~A4), B15.9 (E3)
/~Device RAM: B10.2 (~Device_RAM), B11.23 (~Device_RAM), J4.9
/~Device ROM: B10.5 (~Device_ROM), B11.25 (~Device_ROM), IC2.22 (~CE)
/~Device Registers: B9.4 (~Device_Registers), B10.3 (~Device_Registers), B11.24 (~Device_Registers), B15.4 (~Device_Registers), B23.4 (~Device_Registers)
/~Device Select: B10.11 (~Device_Select), B11.2 (~Device_Select), B16.33 (Deivce_~CS)
/~Enable_{D}: B8.26 (~Enable), J5.B22
/~Horizontal Back Porch End _{CMP}: B12.39 (~B=C), B14.13 (~Back_Porch_End)
/~Horizontal Back Porch Start _{CMP}: B12.28 (~A=C), B14.11 (~Back_Porch_Start)
/~Horizontal Blank: B1.3 (Enable_Pattern), B2.2 (~Load), B14.27 (~Blank)
/~Horizontal Front Porch Start _{CMP}: B3.28 (~A=C), B14.4 (~Front_Porch_Start)
/~Horizontal Sync Start _{CMP}: B3.39 (~B=C), B14.6 (~Sync_Start)
/~Horizontal Sync: B14.20 (~Sync), B20.6 (~Horizontal_Sync)
/~Interrupt_{D}: B8.29 (~INT), J5.B19
/~Memory A: J2.36, J5.B29
/~Memory B: J2.37, J5.B30
/~Pixel CLK_{0}: B14.8 (~CLK), B36.8 (CLK), B37.35 (~Pixel_CLK_{0}), J4.34
/~Pixel CLK_{1}: B2.40 (~CLK), B8.2 (Interrupt_CLK), B37.32 (~Pixel_CLK_{1}), B39.15 (~Pixel_CLK), J4.36
/~Pixel CLK_{2}: B37.28 (~Pixel_CLK_{2}), J4.38
/~Pixel CLK_{3}: B37.25 (~Pixel_CLK_{3}), J4.40
/~RD: B9.15 (~RD), B10.10 (~RD), B15.15 (~RD), B16.46 (~RD), B23.15 (~RD), IC2.24 (~OE), J4.10
/~RD_{D}: B16.20 (~RD_{IN}), J5.B13
/~RD_{M}: J2.23, J5.D10
/~Reset: B1.2 (~Reset), B2.1 (~Reset), B5.1 (~Reset), B11.19 (~Reset_{OUT}), B37.4 (~Reset), J2.34
/~Reset_{D}: B11.15 (~Reset_{IN}), J5.B20
/~Select_{D}: B16.32 (Deivce_~CS_{IN}), J5.B21
/~Vertical Back Porch End: B5.2 (~Load), B7.18 (~Back_Porch_End)
/~Vertical Back Porch End _{CMP}: B7.13 (~Back_Porch_End), B26.31 (~C=A)
/~Vertical Back Porch Start _{CMP}: B7.11 (~Back_Porch_Start), B21.31 (~C=A)
/~Vertical Blank: B7.27 (~Blank), B8.4 (~Set_Interrupt_on_CLK)
/~Vertical Front Porch Start _{CMP}: B6.31 (~C=A), B7.4 (~Front_Porch_Start)
/~Vertical Sync Start _{CMP}: B7.6 (~Sync_Start), B13.31 (~C=A)
/~Vertical Sync: B7.20 (~Sync), B20.16 (~Vertical_Sync)
/~WD: B9.16 (~WD), B10.12 (~WD), B15.16 (~WD), B16.45 (~WD), B23.16 (~WD), IC2.31 (~WE), J4.11
/~WD_{D}: B16.21 (~WD_{IN}), J5.B14
/~WD_{M}: J2.22, J5.D11
unnamed: LED1.1 (K), R3.1
